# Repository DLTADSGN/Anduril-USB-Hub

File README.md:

# Anduril USB Hub
This project is a USB 2.0 Hub with USB C input and three output ports (2 USB A, 1 USB C).

There isn't much novel about this USB Hub, the main challenge was the layout and packaging to get it to fit in the shape of the [Anduril Industries](https://www.anduril.com/) logo:

The PCB is designed to fit in a 3D printed, two part housing that screws together to make the Anduril Industries logo. The upstream/host of the hub is at the top and the downstream/peripheral ports are at the bottom.

## **REQUIREMENTS**:
 - **USB 2.0 minimum**: USB 3.0+ is outside of my skill set currently, so I stuck with USB 2.0 which should be fast enough for most peripherals and data transfer.
 - **A and C ports**: This was trivial but allows the hub to be used for all sorts of devices, including USB C flash drives.
 - **Safety**: Since this is a gift to my coworkers, I wanted the upmost confidence that the devices they plugged in would not get fried by my creation. To ensure this, I added TVS diodes and fuses on every connector for surge protection and over-current protection.
 - **3D printed enclosure**: Since I just got a 3D printer, I wanted to use it to make the housings in the shape of the Anduril logo. This provided me some great practice/challenge in designing PCBs with mechanical constraints. Additionally, this helped me refine a workflow for electro-mechanical integration.

## **WISHLIST**:
### v1.2
- controlled impedence/differential pair routing
- better testing procedure
- downstream UCB C resistors
- fix silkscreen for fuses
### v2.0
- 2 layer for cheaper manufacturing
- controlled impedence/differential pair routing
- better IC selection (USB2514)

## **LICENSE**:
There is **NO** license for reproduction of the Anduril logo. I do not have any rights or permission to reproduce the Anduril logo in any form and am making this at my own risk.

The electronics of Anduril USB Hub</span> by <a xmlns:cc="http://creativecommons.org/ns#" href="https://github.com/colonDdesigns" property="cc:attributionName" rel="cc:attributionURL">colonDdesigns</a> is licensed under a <a rel="license" href="http://creativecommons.org/licenses/by-nc-sa/4.0/">Creative Commons Attribution-NonCommercial-ShareAlike 4.0 International License</a>.

[![CC BY-NC-SA 4.0][cc-by-nc-sa-image]][cc-by-nc-sa]

[cc-by-nc-sa]: http://creativecommons.org/licenses/by-nc-sa/4.0/
[cc-by-nc-sa-image]: https://licensebuttons.net/l/by-nc-sa/4.0/88x31.png

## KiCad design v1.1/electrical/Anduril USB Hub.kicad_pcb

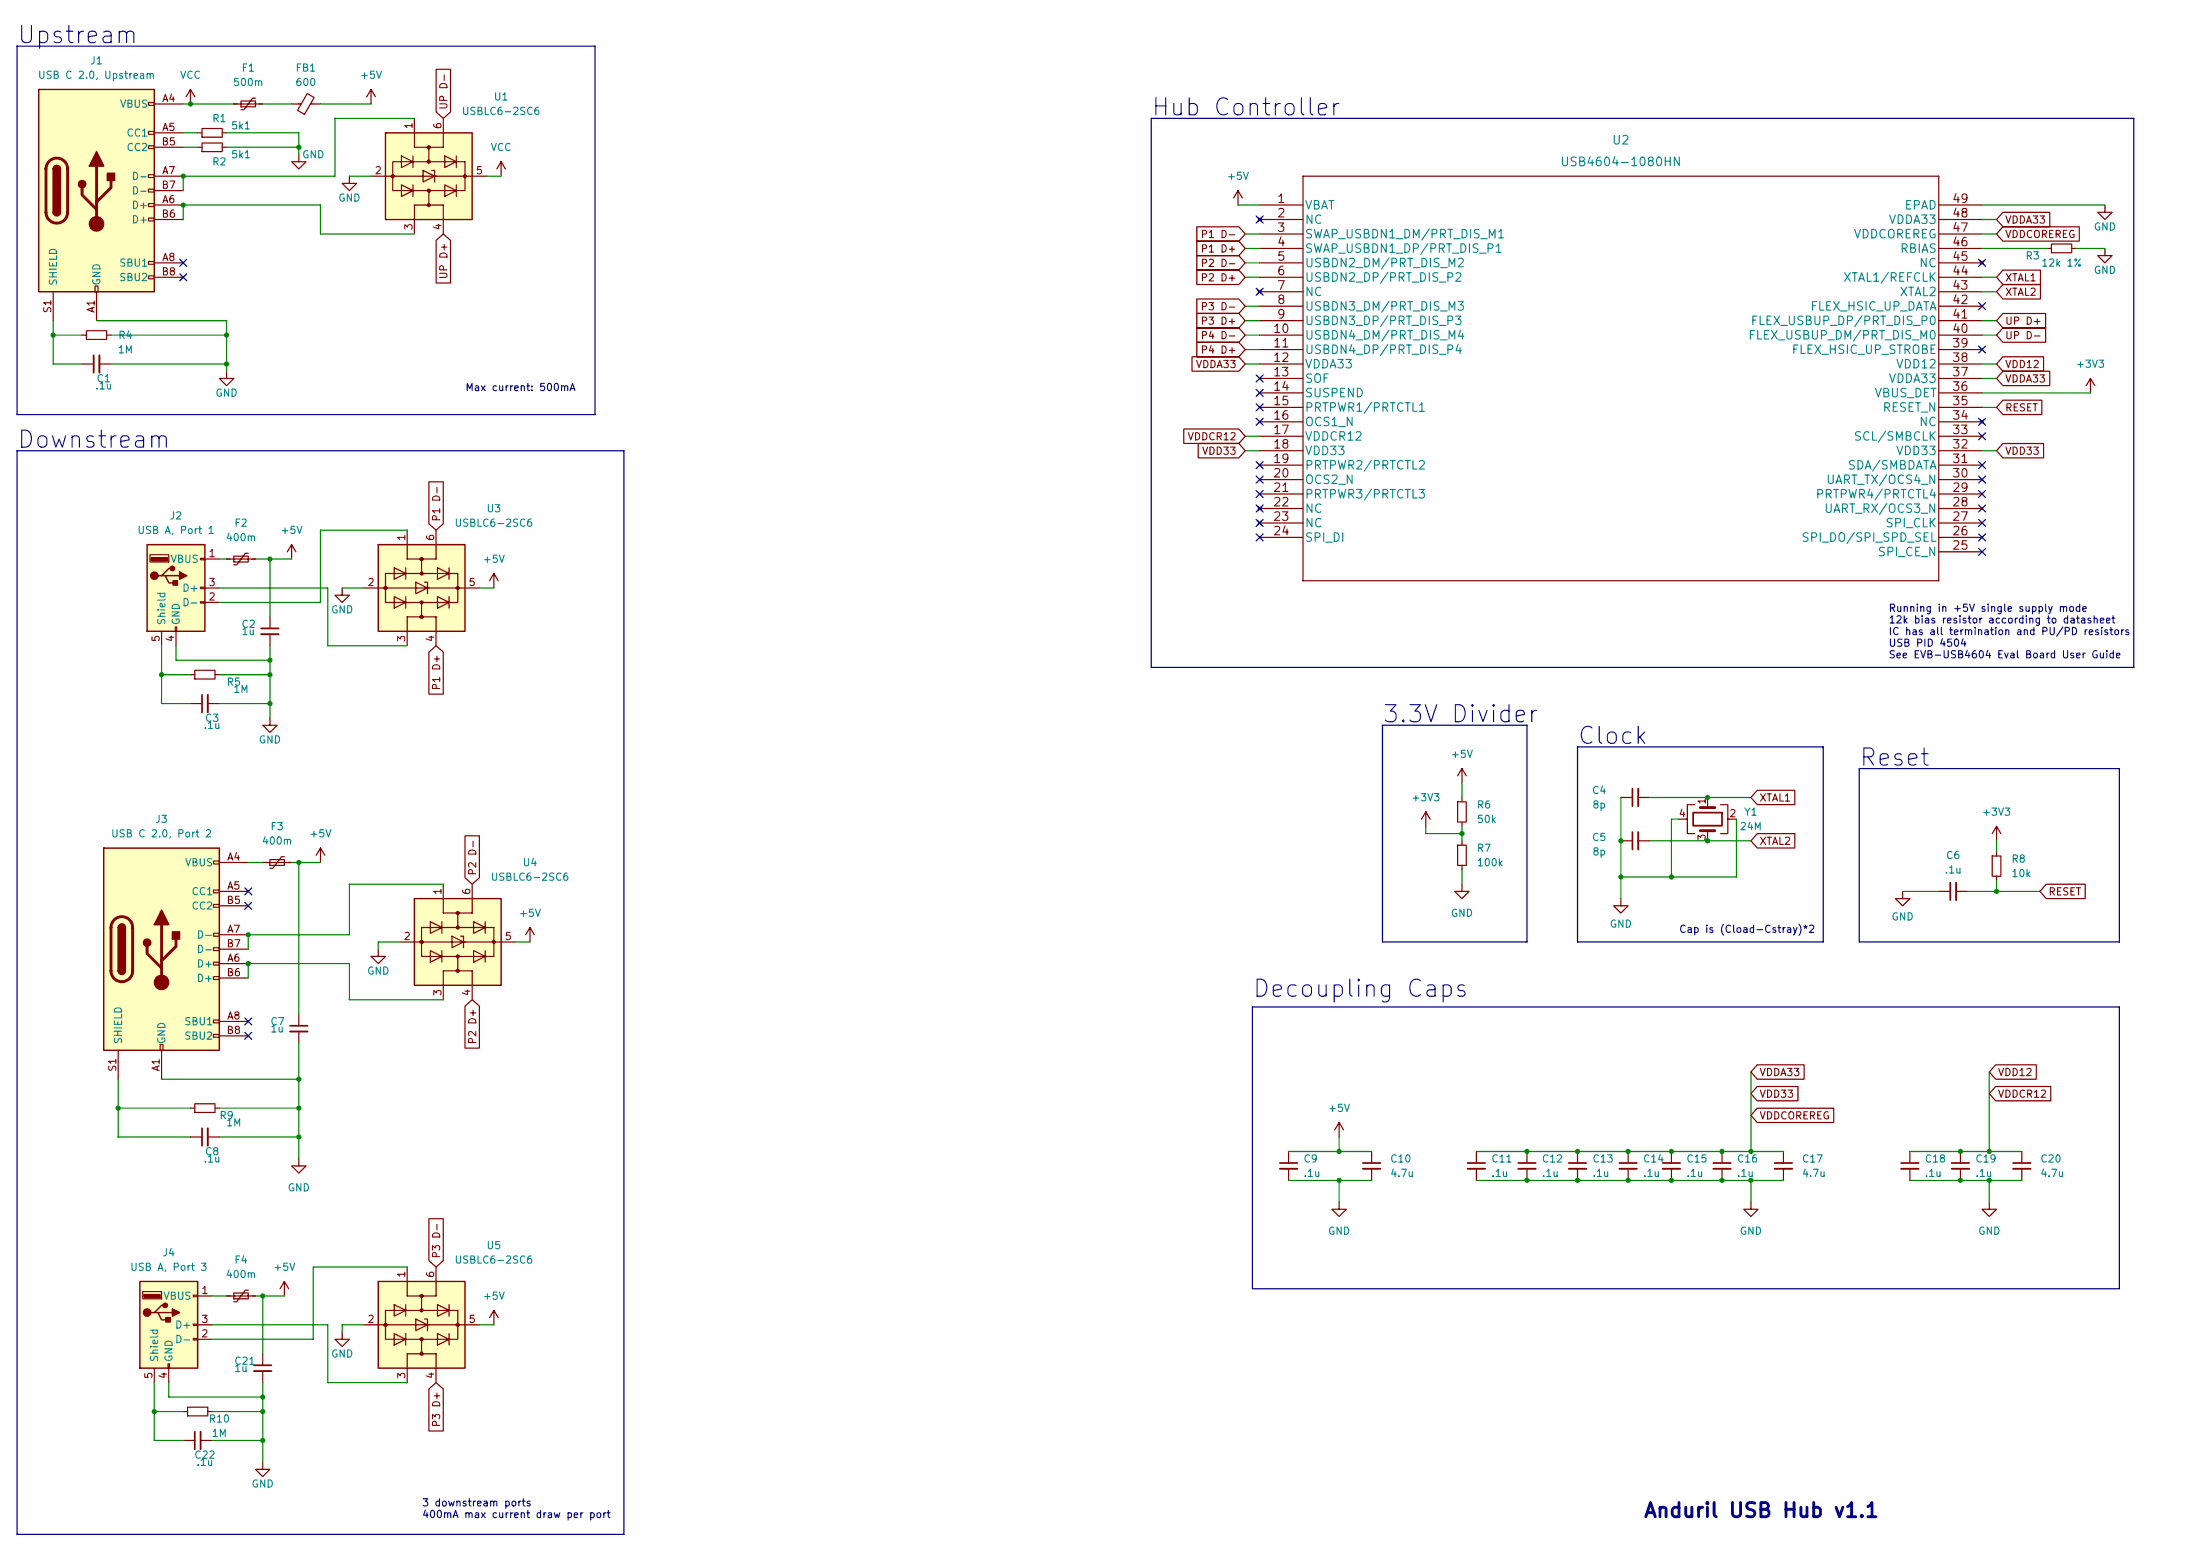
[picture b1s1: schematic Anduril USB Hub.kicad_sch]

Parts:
C1, C3, C6, C8, C9, C11, C12, C13, C14, C15, C16, C18, C19, C22: .1u; C_0805_2012Metric
C2, C7, C21: 1u; C_0805_2012Metric
C4, C5: 8p; C_0805_2012Metric
C10, C17, C20: 4.7u; C_0805_2012Metric
F1: 500m; Fuse_0805_2012Metric
F2, F3, F4: 400m; Fuse_0805_2012Metric
FB1: 600; R_0805_2012Metric
J1: USB C 2.0, Upstream; USB_C_Receptacle_HRO_TYPE-C-31-M-12
J2: USB A, Port 1; USB_A_CONNFLY_DS1095-WNR0
J3: USB C 2.0, Port 2; USB_C_Receptacle_HRO_TYPE-C-31-M-12
J4: USB A, Port 3; USB_A_CONNFLY_DS1095-WNR0
R1, R2: 5k1; R_0805_2012Metric
R3: 12k 1%; R_0805_2012Metric
R4, R5, R9, R10: 1M; R_0805_2012Metric
R6: 50k; R_0805_2012Metric
R7: 100k; R_0805_2012Metric
R8: 10k; R_0805_2012Metric
U1, U3, U4, U5: USBLC6-2SC6; SOT-23-6
U2: USB4604-1080HN; QFN-48-1EP_7x7mm_P0.5mm_EP5.3x5.3mm
Y1: 24M; Crystal_SMD_3225-4Pin_3.2x2.5mm

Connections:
+3V3: R6.2, R7.1, R8.1, U2.36 (VBUS_DET)
+5V: C2.1, C7.1, C9.1, C10.1, C21.1, F2.2, F3.2, F4.2, FB1.2, R6.1, U2.1 (VBAT), U3.5 (VBUS), U4.5 (VBUS), U5.5 (VBUS)
GND: C1.2, C2.2, C3.2, C4.1, C5.1, C6.1, C7.2, C8.2, C9.2, C10.2, C11.2, C12.2, C13.2, C14.2, C15.2, C16.2, C17.2, C18.2, C19.2, C20.2, C21.2, C22.2, J1.A1 (GND), J1.A12 (GND), J1.B1 (GND), J1.B12 (GND), J2.4 (GND), J3.A1 (GND), J3.A12 (GND), J3.B1 (GND), J3.B12 (GND), J4.4 (GND), R1.2, R2.2, R3.2, R4.2, R5.2, R7.2, R9.2, R10.2, U1.2 (GND), U2.49 (EPAD), U3.2 (GND), U4.2 (GND), U5.2 (GND), Y1.2, Y1.4
unnamed: C1.1, J1.S1 (SHIELD), R4.1
unnamed: C3.1, J2.5 (Shield), R5.1
unnamed: C8.1, J3.S1 (SHIELD), R9.1
unnamed: C22.1, J4.5 (Shield), R10.1
unnamed: F1.2, FB1.1
unnamed: F2.1, J2.1 (VBUS)
unnamed: F3.1, J3.A4 (VBUS), J3.A9 (VBUS), J3.B4 (VBUS), J3.B9 (VBUS)
unnamed: F4.1, J4.1 (VBUS)
unnamed: J1.A5 (CC1), R1.1
unnamed: J1.A6 (D+), J1.B6 (D+), U1.3 (I/O2)
unnamed: J1.A7 (D-), J1.B7 (D-), U1.1 (I/O1)
unnamed: J1.B5 (CC2), R2.1
unnamed: J2.2 (D-), U3.1 (I/O1)
unnamed: J2.3 (D+), U3.3 (I/O2)
unnamed: J3.A6 (D+), J3.B6 (D+), U4.3 (I/O2)
unnamed: J3.A7 (D-), J3.B7 (D-), U4.1 (I/O1)
unnamed: J4.2 (D-), U5.1 (I/O1)
unnamed: J4.3 (D+), U5.3 (I/O2)
unnamed: R3.1, U2.46 (RBIAS)
P1 D+: U2.4 (SWAP_USBDN1_DP/PRT_DIS_P1), U3.4 (I/O2)
P1 D-: U2.3 (SWAP_USBDN1_DM/PRT_DIS_M1), U3.6 (I/O1)
P2 D+: U2.6 (USBDN2_DP/PRT_DIS_P2), U4.4 (I/O2)
P2 D-: U2.5 (USBDN2_DM/PRT_DIS_M2), U4.6 (I/O1)
P3 D+: U2.9 (USBDN3_DP/PRT_DIS_P3), U5.4 (I/O2)
P3 D-: U2.8 (USBDN3_DM/PRT_DIS_M3), U5.6 (I/O1)
P4 D+: U2.11 (USBDN4_DP/PRT_DIS_P4)
P4 D-: U2.10 (USBDN4_DM/PRT_DIS_M4)
RESET: C6.2, R8.2, U2.35 (RESET_N)
UP D+: U1.4 (I/O2), U2.41 (FLEX_USBUP_DP/PRT_DIS_P0)
UP D-: U1.6 (I/O1), U2.40 (FLEX_USBUP_DM/PRT_DIS_M0)
VCC: F1.1, J1.A4 (VBUS), J1.A9 (VBUS), J1.B4 (VBUS), J1.B9 (VBUS), U1.5 (VBUS)
VDD12: C18.1, C19.1, C20.1, U2.17 (VDDCR12), U2.38 (VDD12)
VDD33: C11.1, C12.1, C13.1, C14.1, C15.1, C16.1, C17.1, U2.12 (VDDA33), U2.18 (VDD33), U2.32 (VDD33), U2.37 (VDDA33), U2.47 (VDDCOREREG), U2.48 (VDDA33)
XTAL1: C4.2, U2.44 (XTAL1/REFCLK), Y1.1
XTAL2: C5.2, U2.43 (XTAL2), Y1.3

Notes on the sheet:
Clock
Reset
Anduril USB Hub v1.1
Cap is (Cload-Cstray)*2
3.3V Divider
Hub Controller
Upstream
Downstream
Running in +5V single supply mode 12k bias resistor according to datasheet IC has all termination and PU/PD resistors USB PID 4504 See EVB-USB4604 Eval Board User Guide
Decoupling Caps
3 downstream ports 400mA max current draw per port
Max current: 500mA

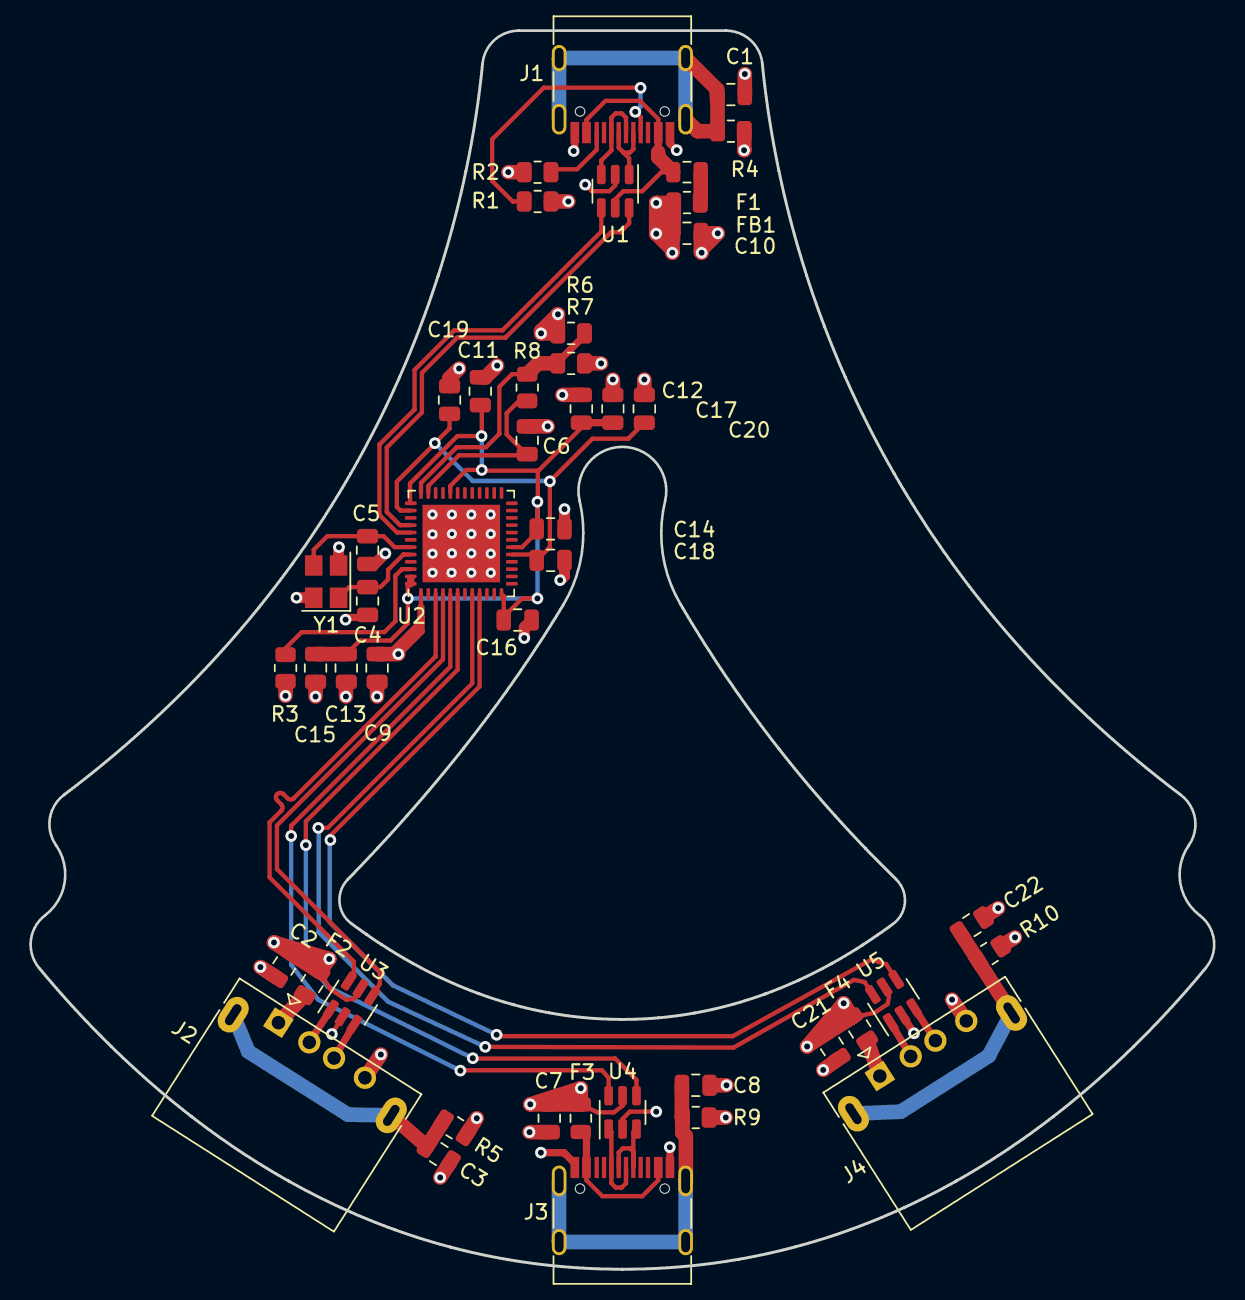
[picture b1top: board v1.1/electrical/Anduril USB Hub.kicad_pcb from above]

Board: 4 copper layers, 80.8 x 84.6 mm, 47 parts (0 on the bottom side), 36 nets.

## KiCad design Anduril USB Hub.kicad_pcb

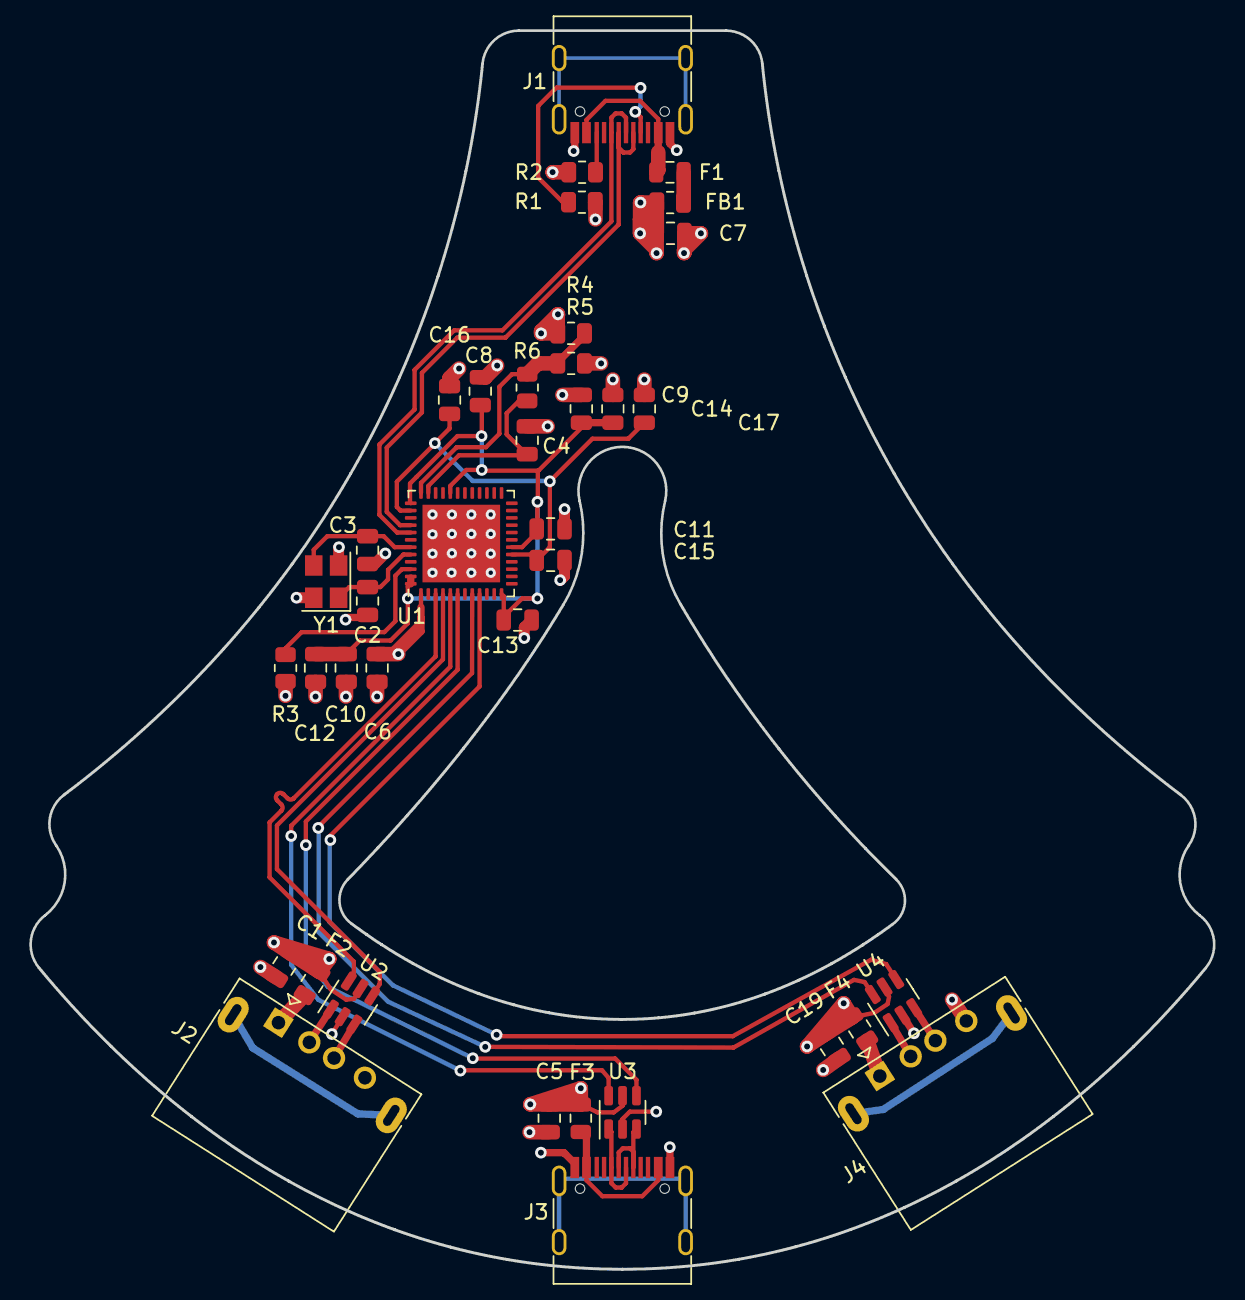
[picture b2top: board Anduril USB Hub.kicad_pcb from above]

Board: 4 copper layers, 80.8 x 84.6 mm, 38 parts (0 on the bottom side), 30 nets.

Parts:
C1, C5, C19: 1u; C_0805_2012Metric
C2, C3: 8p; C_0805_2012Metric
C4, C6, C8, C9, C10, C11, C12, C13, C15, C16: .1u; C_0805_2012Metric
C7, C14, C17: 4.7u; C_0805_2012Metric
F1: 1; Fuse_0805_2012Metric
F2, F3, F4: 900m; Fuse_0805_2012Metric
FB1: 600; R_0805_2012Metric
J1: USB C 2.0, Upstream; USB_C_Receptacle_HRO_TYPE-C-31-M-12
J2: USB A, Port 1; USB_A_CONNFLY_DS1095-WNR0
J3: USB C 2.0, Port 2; USB_C_Receptacle_HRO_TYPE-C-31-M-12
J4: USB A, Port 3; USB_A_CONNFLY_DS1095-WNR0
R1, R2: 5k1; R_0805_2012Metric
R3: 12k 1%; R_0805_2012Metric
R4: 50k; R_0805_2012Metric
R5: 100k; R_0805_2012Metric
R6: 10k; R_0805_2012Metric
U1: USB4604-1080HN; QFN-48-1EP_7x7mm_P0.5mm_EP5.3x5.3mm
U2, U3, U4: USBLC6-2SC6; SOT-23-6
Y1: 24M; Crystal_SMD_3225-4Pin_3.2x2.5mm

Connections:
+3V3: R4.2, R5.1, R6.1, U1.36 (VBUS_DET)
+5V: C1.1, C5.1, C6.1, C7.1, C19.1, F2.2, F3.2, F4.2, FB1.2, R4.1, U1.1 (VBAT), U2.5 (VBUS), U3.5 (VBUS), U4.5 (VBUS)
GND: C1.2, C2.1, C3.1, C4.1, C5.2, C6.2, C7.2, C8.2, C9.2, C10.2, C11.2, C12.2, C13.2, C14.2, C15.2, C16.2, C17.2, C19.2, J1.A1 (GND), J1.A12 (GND), J1.B1 (GND), J1.B12 (GND), J2.4 (GND), J3.A1 (GND), J3.A12 (GND), J3.B1 (GND), J3.B12 (GND), J4.4 (GND), R1.2, R2.2, R3.2, R5.2, U1.49 (EPAD), U2.2 (GND), U3.2 (GND), U4.2 (GND), Y1.2, Y1.4
unnamed: F1.2, FB1.1
unnamed: F2.1, J2.1 (VBUS)
unnamed: F3.1, J3.A4 (VBUS), J3.A9 (VBUS), J3.B4 (VBUS), J3.B9 (VBUS)
unnamed: F4.1, J4.1 (VBUS)
unnamed: J1.A5 (CC1), R1.1
unnamed: J1.B5 (CC2), R2.1
unnamed: J2.2 (D-), U2.1 (I/O1)
unnamed: J2.3 (D+), U2.3 (I/O2)
unnamed: J3.A6 (D+), J3.B6 (D+), U3.3 (I/O2)
unnamed: J3.A7 (D-), J3.B7 (D-), U3.1 (I/O1)
unnamed: J4.2 (D-), U4.1 (I/O1)
unnamed: J4.3 (D+), U4.3 (I/O2)
unnamed: R3.1, U1.46 (RBIAS)
P1 D+: U1.4 (SWAP_USBDN1_DP/PRT_DIS_P1), U2.4 (I/O2)
P1 D-: U1.3 (SWAP_USBDN1_DM/PRT_DIS_M1), U2.6 (I/O1)
P2 D+: U1.6 (USBDN2_DP/PRT_DIS_P2), U3.4 (I/O2)
P2 D-: U1.5 (USBDN2_DM/PRT_DIS_M2), U3.6 (I/O1)
P3 D+: U1.9 (USBDN3_DP/PRT_DIS_P3), U4.4 (I/O2)
P3 D-: U1.8 (USBDN3_DM/PRT_DIS_M3), U4.6 (I/O1)
RESET: C4.2, R6.2, U1.35 (RESET_N)
UP D+: J1.A6 (D+), J1.B6 (D+), U1.41 (FLEX_USBUP_DP/PRT_DIS_P0)
UP D-: J1.A7 (D-), J1.B7 (D-), U1.40 (FLEX_USBUP_DM/PRT_DIS_M0)
VCC: F1.1, J1.A4 (VBUS), J1.A9 (VBUS), J1.B4 (VBUS), J1.B9 (VBUS)
VDD12: C15.1, C16.1, C17.1, U1.17 (VDDCR12), U1.38 (VDD12)
VDD33: C8.1, C9.1, C10.1, C11.1, C12.1, C13.1, C14.1, U1.12 (VDDA33), U1.18 (VDD33), U1.32 (VDD33), U1.37 (VDDA33), U1.47 (VDDCOREREG), U1.48 (VDDA33)
XTAL1: C2.2, U1.44 (XTAL1/REFCLK), Y1.1
XTAL2: C3.2, U1.43 (XTAL2), Y1.3

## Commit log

2022-11-26 blah blah comment
2022-12-03 layout done, saving for 0805 change
2022-12-06 V1.0
2022-12-20 v1.1 WIP
2022-12-27 formatting
2022-12-28 readme updates
2022-12-28 housekeeping
2022-12-28 image resizing
2023-01-04 cleanup
2023-01-04 added photos
2023-01-08 more docs
2023-01-08 added sw parts
2023-01-08 Squashed commit of the following:
    commit f22f3198f381777f4f66884274b8b2f045b28ac8
    Author: sethldaly <seth.daly7531@gmail.com>
    Date: Sat Jan 7 21:56:58 2023 -0800
    added sw parts
    commit 5dc11b7028ca124676168761a285e70834db4c27
    Author: sethldaly <seth.daly7531@gmail.com>
